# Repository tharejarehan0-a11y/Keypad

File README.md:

# Keypad
<br>

<br>

# **Keyboard for Beginners**
(_It is Keypad a keyboard designed specifically to make learning touch typing efficient and more easy for beginners_)

<br>

<br>

# **Story Behind it/Motivation**
When I started my computer journey I started learning how to do typing fast (_touch typing_). I was made to type only alphabets in the whole course some or the other way for me there was like no use of other keys similarly for many people other keys are just useless when they want to learn typing or practice it **and it is specifically designed for it**

# **Key takeaways**

1. Best for people starting touch typing
2. More portable if only learning to type
3. Mechanical keyboard with MX Cherry Keys
4. Can be customized using the firmware unlike ordinary keyboards

# **Schematics**

# Matrix
<br>

<br><br>

**These keys are layed in a matrix of rows and columns. There are 10 columns and 4 rows in the matrix. All the intersection of the rows and columns constitute a key here. The microconttroller that will be attached to these will detect low currect at the key you will press and will have already the columns and rows assigned in the firmware that let it know where the key to detect is. I have attached global labels of rows and columns which can be attached to the microcontroller and help the schematics look a lot cleaner**

<br><br>
# Keys
<br>

<br><br>
**The key composes of a keyswitch and a diode these help the microcontroller help detect the lower currect in the matrix of rows and columns**

<br><br>
# Microcontroller
<br>

<br><br>
**As a microcontroller we are using the raspberry pi pico which has 22 gpio pins the net lablels or the global net labels are attached to these pins only. The ADC_VREF pin is the analog to digital converter the 3.3v is fed into this pin but has lot of noise that is why we add a capatior of 100nF here. Then we have the 3v3 pin and the run pin . The run pin is connected to a sw_push button with one end of the push button connected to gnd and other end free and the 3v3 pin is essentially the pin that gives out the the 3v3 current it has two capacitors parallely of 100nF and 10µF to reduce the noise you can check out the design at mech_keyboard.kicad_sch**

<br><br>

# **PCB Design**
<br>

<br>

**This is the PCB Design of the keyboard having the footprints of keys of MX_Cherry , The Raspberry pi pico, resistors_smd_do35, sw_push_button and capacitors. There are also mounting holes on the pcb for the screws to fit in . We will be using the m2 screws having dimensions 2mm * 6mm and 2mm * 8mm for it . The routing follows the pattern that the capacitors , sw_push and resistors are done in the front chopper layer and the columns in the back chopper layer but there are vias also present in the pcb which make it hetrogeneous.<br><br>We have used to grind one is 19.05mm and other is 2.3813mm. the first was used for the keys which were moved by reference to it's upper right corner and the second was used for resistors which were moved without any resistors. You can check out the design in mech_Keyboard.kicad_pcb**

# **CAD**
<br>

<br>

**Go to https://www.keyboard-layout-editor.com/ to design a keyboard here we designed it complementing to our pcb and schematics paste this in the raw data tab of the site** 

<br>
<br>

```
  [{ "a": 7 }, "", "", "", "", "", { "x": 3 }, "", "", "", "", ""],
  ["", "", "", "", "", { "x": 3 }, "", "", "", "", ""],
  [{ "x": 1 }, "", "", "", "", { "x": 3 }, "", "", "", ""],
  [{ "x": 3, "w": 7 }, ""]
```

<br>

**then go to https://swillkb.com/ and paste the either the raw data of your design under the raw data tab or paste this onto the website u will get a dxf file which you can also take from the files here**

**Note: I have made some changes in the sketch according to my design you can find those sketches in 3D_Models >> DXF**

# Onshape

<br>

<br>

**Done everything in Onshape you can see all the files related to it go to 3D_Models >> STEP and if you want to see the sketches that will be in 3D_Models >> DXF and the link to onshape is https://cad.onshape.com/documents/34256bf3e585af5c7248ec84/w/d1b125939af1c93ac5709ce3/e/966044b3990b03ffc888e75f?renderMode=0&uiState=6a1d9bf18f13d1741420cc5c this you can have a look at it**

<br>

# **firmware**

<br>

<br>

**The firmware is written in Circuit python and has KMK library used to program the keyboard the keymap array is used to assign the keys to the intersection and the rows and columns are denoted by keyboard.row_pins and keyboard.col_pins and we have a name function which loads the code onto the keyboard.**

<br>

# **Components**

1. **Raspberry pi pico**
2. **MX Cherry 1.00u Keys and Keycaps**
3. **MX Cherry 7.00u Keycap and stablizer**
4. **PCB**
5. **DO-35 Resistors**
6. **SMD C_0603_1608Metric Capacitors**
7. **SW_Push Button**
8. **M2 2mm*6mm screws**

<br>

# **BOM**
**Sidenote for reviewers**
_(There is a chance that ktron.in does not accept the hcb money if it happens then i will pay my self)_

| #  | Company                              | Part                                 | Quantity |   Price  | Link                                                                                              |
|----|--------------------------------------|--------------------------------------|-------|----------|---------------------------------------------------------------------------------------------------|
| 1  | JLCPCB                               | PCB                                  | 1     | 12.25$    | https://www.jlcpcb.com    |                                                |
| 2  | Robocraze                            | Raspberry Pi Pico                    | 1     | ₹400     | https://robocraze.com/products/raspberry-pi-pico?_pos=2&_sid=2e551ee8b&_ss=r                      |
| 3  | Robocraze                            | Male Headers (40x1 pin 2.54mm pitch) | 2     | ₹20      | https://robocraze.com/products/40x1-pin-2-54mm-pitch-male-berg-strip?_pos=11&_sid=5a10e633c&_ss=r |
| 4  | robu.in                              | 1N4148 Diodes                        | 30    | ₹180     | https://robu.in/product/1n4148-t50a-onsemi-100v-1v10ma-4ns-200ma-do-35-switching-diodes-rohs      |
| 5  | KTRON                                | SMD 0603 Capacitors 100nF            | 25    | ₹20      | https://www.ktron.in/product/100nf-50v-104-mlcc-0603/?v=2978dbfa7f71                              |
| 6  | robu.in                              | SMD 0603 Capacitors 10uF             | 5     | ₹20      | https://robu.in/product/10uf-10000nf-50v-capacitor-0603-smd-package-pack-of-5                     |
| 7  | Stackskb.com                         | MX Cherry Keyswitches                | 45    | ₹1200    | https://stackskb.com/store/akko-botany-switch-pack-of-45/                                         |
| 8  | Curiosity Caps                       | MX Cherry Keycaps                    | 130+  | ₹2500    | http://curiositycaps.in/products/manga-theme-cherry-pbt-keycaps?variant=50211931226393            |
| 9  | Printing Legion India (via HackClub) | Case                                 | 1     | $2       | https://hackclub.com                                                                              |
| 10 | OnlyScrews                           | M2x6mm Screws                        | 25    | ₹105     | https://onlyscrews.in/products/m2-x-6mm-phillips-round-head-laptop-screw?variant=49369266192697   |
| 11 | OnlyScrews                           | M2x8mm Screws                        | 25    | ₹110     | https://onlyscrews.in/products/m2-x-8mm-phillips-round-head-laptop-screw-1?variant=49693360423225 |
| 12 | OnlyScrews                           | M2 Nuts                              | 25    | ₹150     | https://onlyscrews.in/products/m2-nyloc-nuts-ss304-dia-2mm?variant=50164298645817                 |
| 13 | Stackskb.com                         | Stabilizers                          | 4+1   | ₹1595    | https://stackskb.com/store/durock-clear-screw-in-stabilizers-v2/                |
| 14 | Robocraze                            | SW_Push Buttons                      | 25    | ₹25      | https://robocraze.com/products/4-pin-push-button-tactile-switch-12x12x15mm-pack-of-5?_pos=6&_sid=3446358db&_ss=r   |
| 15 | Shipping&Taxes                       | N/A                                  | All   | ₹700+39$ | N/A                                                                                               |

<br>

# **files**

<br>

1. **Readme.md** : explanation of all the project <br>
2. **Kicad** : All the Kicad related files <br> 
3. **Production Files** : Contains all the fabrication files used in the pcb manufacturing process <br>
4. **firmware** : This contains the firmware for the keyboard to be used <br>
5. **3D_Models*** : All the assets needed for 3D printing and all the sketches and 3D Models <br>
6. **Assets_Kicad** : All the assets needed for the schematics and pcb design including the 3d models, footprints, schematic symbols <br>
7. **Zinepage.png** : has the A5 Design for the fallout zine <br>

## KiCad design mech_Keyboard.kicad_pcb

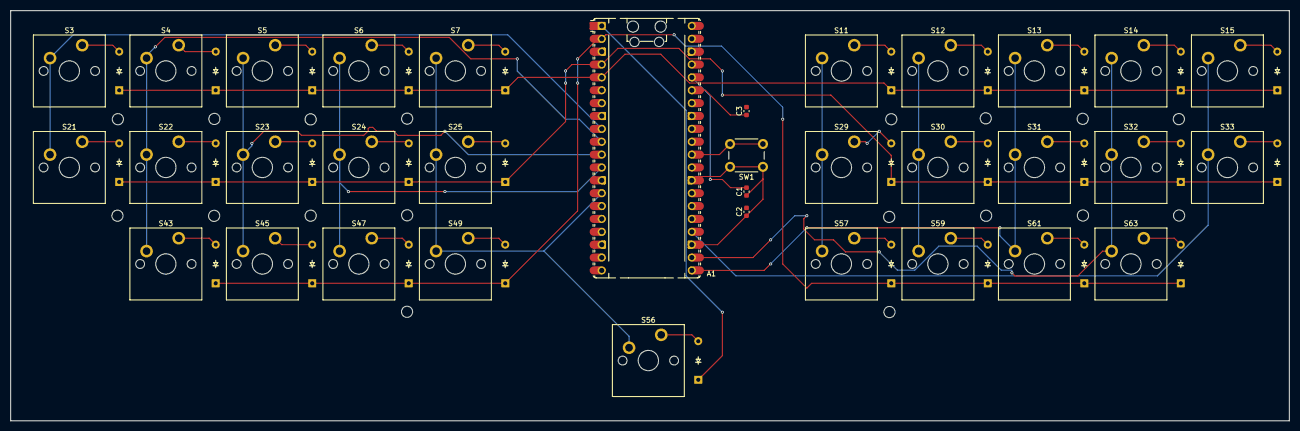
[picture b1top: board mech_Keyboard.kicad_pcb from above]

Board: 2 copper layers, 252.4 x 81.0 mm, 63 parts (0 on the bottom side), 47 nets.

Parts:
A1: RaspberryPi_Pico; RaspberryPi_Pico_Common_Unspecified
C1, C3: 100nF; C_0603_1608Metric
C2: 10µF; C_0603_1608Metric
D3, D4, D5, D6, D7, D11, D12, D13, D14, D15, D21, D22, D23, D24, D25, D29, D30, D31, D32, D33, D43, D45, D47, D49, D56, D57, D59, D61, D63: Diode_DO-35
S3, S4, S5, S6, S7, S11, S12, S13, S14, S15, S21, S22, S23, S24, S25, S29, S30, S31, S32, S33, S43, S45, S47, S49, S57, S59, S61, S63: MX_PCB_1.00u
S56: MX_PCB_7.00u
SW1: SW_Push; SW_PUSH_6mm_H5mm

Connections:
COLUMN3: A1.9 (GPIO6), S3.1, S21.1
COLUMN4: A1.10 (GPIO7), S4.1, S22.1, S43.1
COLUMN5: A1.11 (GPIO8), S5.1, S23.1, S45.1
COLUMN6: A1.12 (GPIO9), S6.1, S24.1, S47.1
COLUMN7: A1.14 (GPIO10), S7.1, S25.1, S49.1, S56.1
COLUMN11: A1.19 (GPIO14), S11.1, S29.1, S57.1
COLUMN12: A1.20 (GPIO15), S12.1, S30.1, S59.1
COLUMN13: A1.21 (GPIO16), S13.1, S31.1, S61.1
COLUMN14: A1.22 (GPIO17), S14.1, S32.1, S63.1
COLUMN15: A1.24 (GPIO18), S15.1, S33.1
GND: A1.3 (GND), A1.8 (GND), A1.13 (GND), A1.18 (GND), A1.23 (GND), A1.28 (GND), A1.33 (AGND), A1.38 (GND), C1.1, C2.1, SW1.1
unnamed: A1.36 (3V3), C1.2, C2.2
unnamed: A1.35 (ADC_VREF), C3.1
unnamed: A1.30 (RUN), SW1.2
unnamed: D3.2 (A), S3.2
unnamed: D4.2 (A), S4.2
unnamed: D5.2 (A), S5.2
unnamed: D6.2 (A), S6.2
unnamed: D7.2 (A), S7.2
unnamed: D11.2 (A), S11.2
unnamed: D12.2 (A), S12.2
unnamed: D13.2 (A), S13.2
unnamed: D14.2 (A), S14.2
unnamed: D15.2 (A), S15.2
unnamed: D21.2 (A), S21.2
unnamed: D22.2 (A), S22.2
unnamed: D23.2 (A), S23.2
unnamed: D24.2 (A), S24.2
unnamed: D25.2 (A), S25.2
unnamed: D29.2 (A), S29.2
unnamed: D30.2 (A), S30.2
unnamed: D31.2 (A), S31.2
unnamed: D32.2 (A), S32.2
unnamed: D33.2 (A), S33.2
unnamed: D43.2 (A), S43.2
unnamed: D45.2 (A), S45.2
unnamed: D47.2 (A), S47.2
unnamed: D49.2 (A), S49.2
unnamed: D56.2 (A), S56.2
unnamed: D57.2 (A), S57.2
unnamed: D59.2 (A), S59.2
unnamed: D61.2 (A), S61.2
unnamed: D63.2 (A), S63.2
ROW1: A1.1 (GPIO0), D56.1 (K)
ROW2: A1.2 (GPIO1), D43.1 (K), D45.1 (K), D47.1 (K), D49.1 (K), D57.1 (K), D59.1 (K), D61.1 (K), D63.1 (K)
ROW3: A1.4 (GPIO2), D21.1 (K), D22.1 (K), D23.1 (K), D24.1 (K), D25.1 (K), D29.1 (K), D30.1 (K), D31.1 (K), D32.1 (K), D33.1 (K)
ROW4: A1.5 (GPIO3), D3.1 (K), D4.1 (K), D5.1 (K), D6.1 (K), D7.1 (K), D11.1 (K), D12.1 (K), D13.1 (K), D14.1 (K), D15.1 (K)

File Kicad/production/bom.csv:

Designator,Footprint,Quantity,Value,LCSC Part #
A1,RaspberryPi_Pico_Common_Unspecified,1,RaspberryPi_Pico,
"C1, C3",0603,2,100nF,
C2,0603,1,10µF,
"D11, D12, D13, D14, D15, D21, D22, D23, D24, D25, D29, D3, D30, D31, D32, D33, D4, D43, D45, D47, D49, D5, D56, D57, D59, D6, D61, D63, D7",Diode_DO-35,29,~,
"S11, S12, S13, S14, S15, S21, S22, S23, S24, S25, S29, S3, S30, S31, S32, S33, S4, S43, S45, S47, S49, S5, S57, S59, S6, S61, S63, S7",MX_PCB_1.00u,28,~,
S56,MX_PCB_7.00u,1,~,
SW1,SW_PUSH_6mm_H5mm,1,SW_Push,

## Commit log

2026-04-22 Intialization
    Added all the files to the repo
2026-04-23 assets added
2026-04-23 finalized changes
2026-04-23 Add gerber archive and BOM; update PCB files
    Add an Archive/ folder containing generated Gerber (F/Cu, mask, paste, silkscreen), edge cuts, and drill files plus Archive.zip and .DS_Store; add BOM.csv. Update mech_Keyboard.kicad_pcb and mech_Key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
2026-04-23 fixed bom
2026-04-23 Add new screenshot to README
    Added a new image to the README for better visual representation.
2026-04-23 Add project files section to README
    Added a section listing project files and their descriptions.
2026-04-23 Revise file list format in README.md
    Updated the file list in README.md with numbering and line breaks.
2026-04-23 Add new items to BOM with pricing and links
2026-04-23 Update quantities for OnlyScrews items in BOM
2026-04-23 added zine page
2026-04-23 renamed
2026-04-23 Add Zinepage.png description to README
2026-04-23 Refactor BOM.csv with new header format
    Updated BOM.csv to a new format with headers and corrected links.
2026-04-23 Change header for 'Story Behind it' to 'Story Behind it/Motivation'
    Updated section header for clarity and emphasis.
2026-04-23 modified bom
2026-04-25 Change PCB price and source in BOM.csv
    Updated PCB price and supplier link in BOM.
2026-04-25 Change PCB price in BOM.csv
    Updated the price of PCB from $27 to $30-80.
2026-04-25 Remove price and quantity from BOM.csv
    Removed price and quantity information from BOM.csv entries.
2026-04-28 Revise BOM with quantities and updated prices
    Updated BOM.csv with quantities and prices in INR.
2026-04-28 Remove shipping note from BOM.csv
    Removed the line indicating that shipping is not included.
2026-04-28 Change BOM file from BOM.md to BOM.csv
    Updated BOM file reference from BOM.md to BOM.csv and added note about shipping.
2026-04-28 Add shipping and taxes entry to BOM.csv
2026-05-01 organization
2026-05-01 Revise Kicad and assets section in README
    Updated file names and descriptions for clarity.
2026-05-01 Update README with additional images
    Added new images to enhance the README content.
2026-05-01 Add BOM section with components and links
2026-05-01 bom.csv deleted
2026-05-01 Revise asset names and BOM details in README
    Updated asset names and added new components to the BOM.
2026-05-03 Update PCB supplier and shipping cost in README
2026-05-03 Reorganize project file list in README.md
2026-05-03 Fix JLCPCB link in BOM.csv
    Updated the link for JLCPCB in BOM.csv.
2026-05-31 troubleshooting
2026-05-31 Revise README for design updates and file structure
    Updated README to reflect changes in design sketches and file organization.
2026-05-31 added zip
2026-06-01 Replace old image with new screenshot
    Updated image in README and improved formatting.
2026-06-01 Update image in README
    Replaced the old image with a new screenshot in the README.
2026-06-01 Update README with Onshape document link
    Added a link to the Onshape document for better access.
2026-06-01 did some stuff with organising
2026-06-01 organised
